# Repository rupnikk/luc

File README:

Urban Rupnik
1.12.2016
Zadlog 42

Popravilo luči:
-nastavitev avtomatskega odklopa luči napetosti na tranzistorju pod 5.5V
-omejilnik toka -> 380 mA.
-upor R je za hitrost prehoda in strmino linearnosti
-VCE za nastavitev toka -> max 0. -> R=2.24
-Precejšen padec napetosti, višji napajalnik
-zaščita -> varovalka 3A
-širina vezja = 2.5 mm

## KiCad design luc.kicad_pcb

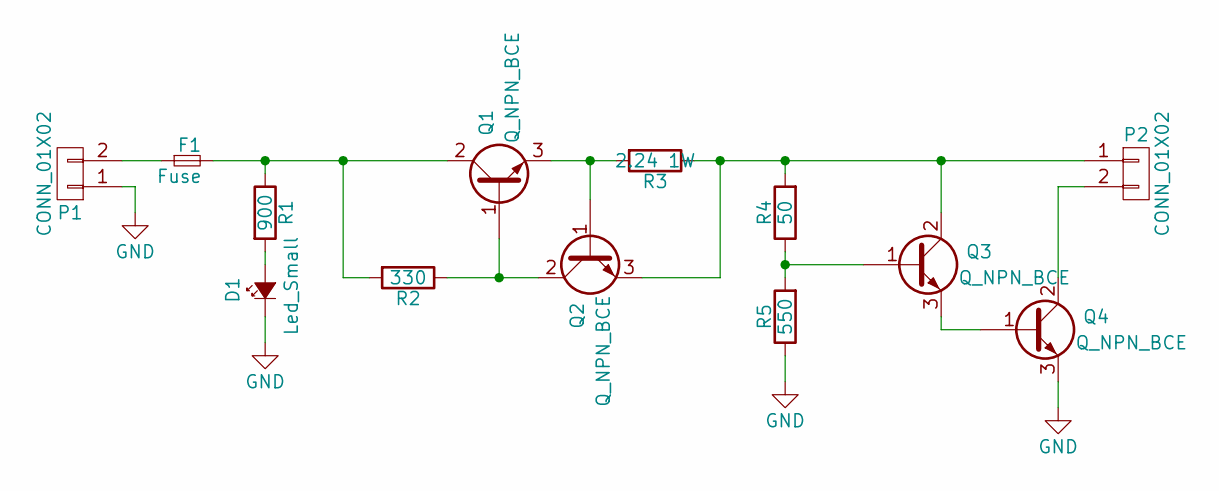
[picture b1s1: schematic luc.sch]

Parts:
D1: Led_Small; Conector_holes_2.54
F1: Fuse; Fuseholder_Fuse_5x15; Farnell number 1848686
P1, P2: CONN_01X02; Conector_holes_2.54
Q1, Q2, Q3, Q4: Q_NPN_BCE; SOT89-3_Housing_Handsoldering; Farnell number 8736359
R1: 900; R_0805_HandSoldering
R2: 330; R_0805_HandSoldering
R3: 2.24 1W; Resistor_Horizontal_RM15mm
R4: 50; R_0603_HandSoldering
R5: 550; R_0805_HandSoldering

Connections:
GND: D1.1 (K), P1.1, Q4.3 (E), R5.1
unnamed: D1.2 (A), R1.2
unnamed: F1.1, P1.2
unnamed: F1.2, Q1.2 (C), R1.1, R2.2
unnamed: P2.1, Q2.3 (E), Q3.2 (C), R3.1, R4.2
unnamed: P2.2, Q4.2 (C)
unnamed: Q1.1 (B), Q2.2 (C), R2.1
unnamed: Q1.3 (E), Q2.1 (B), R3.2
unnamed: Q3.1 (B), R4.1, R5.2
unnamed: Q3.3 (E), Q4.1 (B)

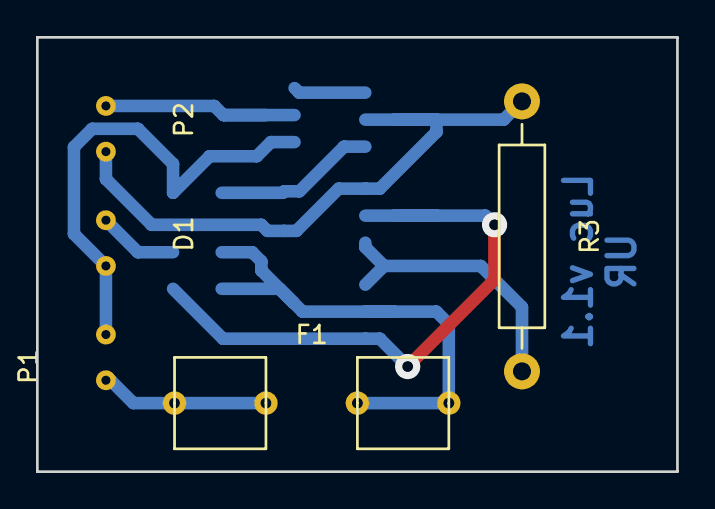
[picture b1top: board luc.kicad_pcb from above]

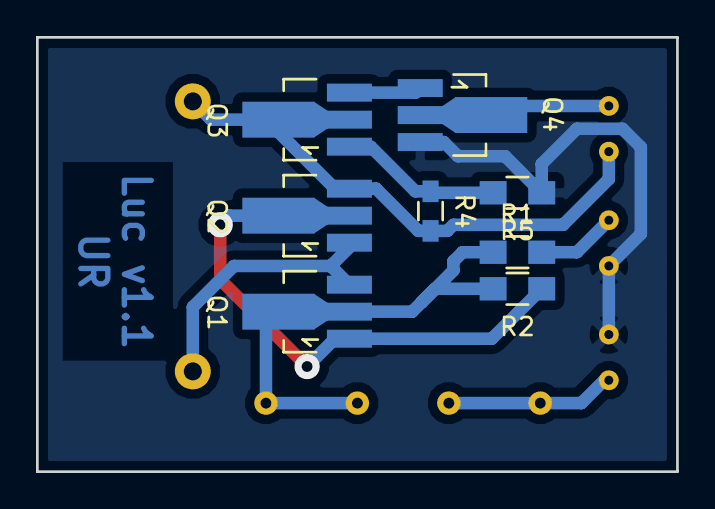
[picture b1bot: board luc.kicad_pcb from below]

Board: 2 copper layers, 35.6 x 24.1 mm, 13 parts (8 on the bottom side), 10 nets.

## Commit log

2016-12-01 Protorip
